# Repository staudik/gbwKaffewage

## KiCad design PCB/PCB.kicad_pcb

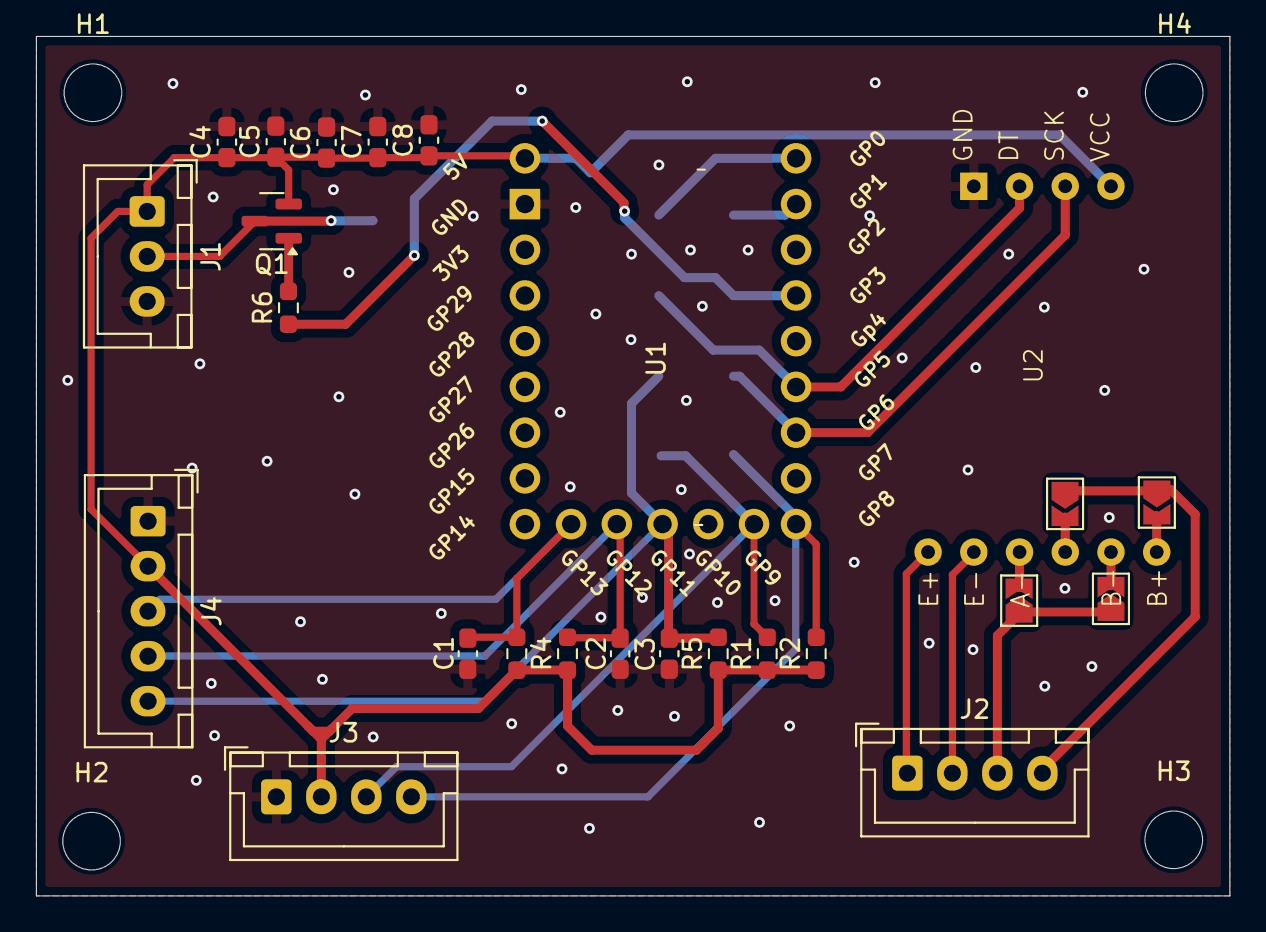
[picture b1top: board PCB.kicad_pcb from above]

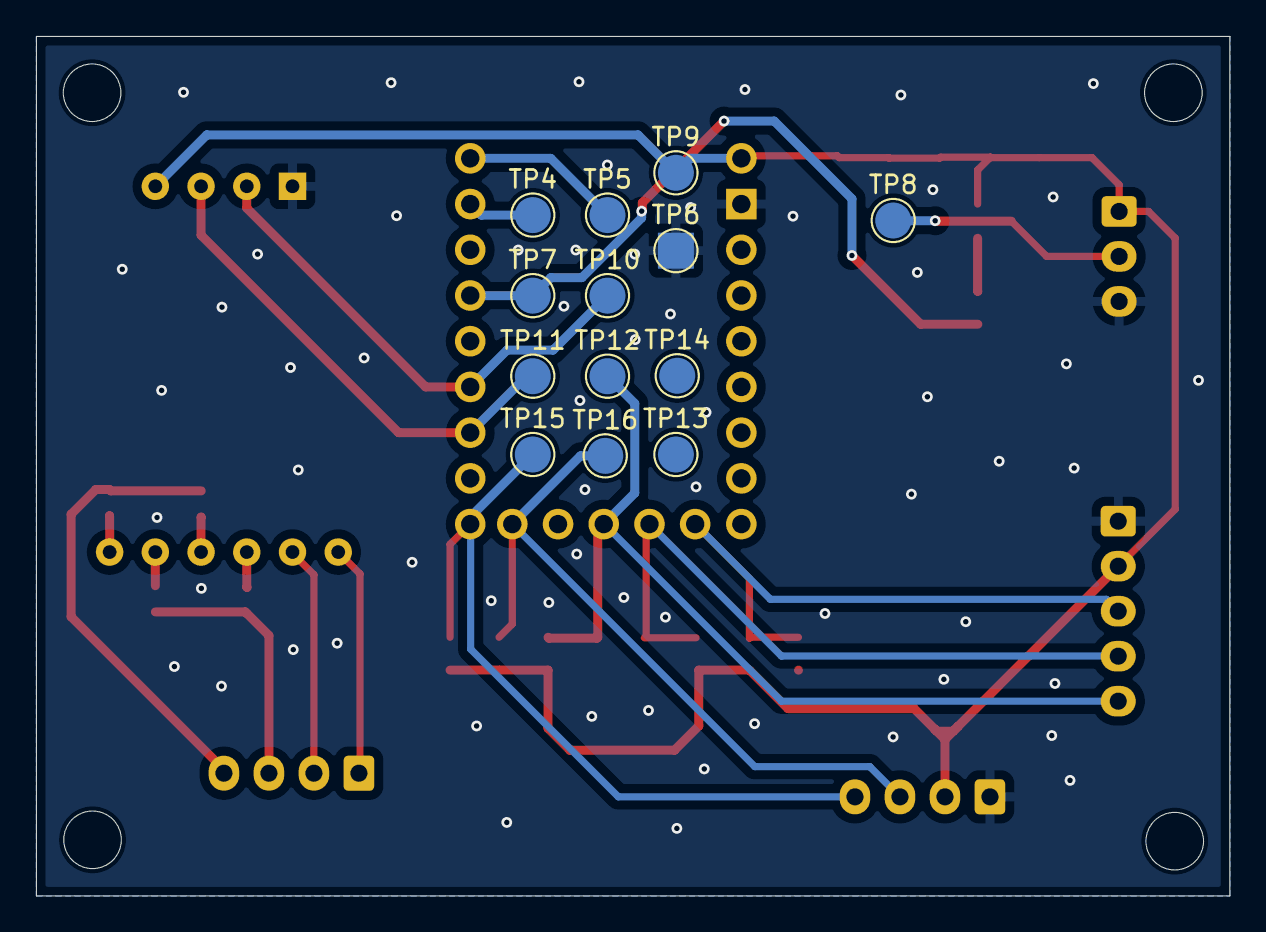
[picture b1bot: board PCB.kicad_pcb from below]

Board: 2 copper layers, 66.3 x 47.8 mm, 42 parts (13 on the bottom side), 22 nets.

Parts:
C1, C2, C3: 100n; C_0603_1608Metric_Pad1.08x0.95mm_HandSolder
C4, C5, C6, C7, C8: C; C_0603_1608Metric_Pad1.08x0.95mm_HandSolder
H1, H2, H3, H4: MountingHole; MountingHole_3.2mm_M3_DIN965
J1: Conn_01x03_Pin; JST_XH_B3B-XH-A_1x03_P2.50mm_Vertical
J2: Conn_01x04_Pin; JST_XH_B4B-XH-A_1x04_P2.50mm_Vertical
J3: Conn_01x04_Socket; JST_XH_B4B-XH-A_1x04_P2.50mm_Vertical
J4: Conn_01x05_Socket; JST_XH_B5B-XH-A_1x05_P2.50mm_Vertical
JP1, JP2, JP3, JP4: SolderJumper_2_Open; SolderJumper-2_P1.3mm_Open_TrianglePad1.0x1.5mm
Q1: BC807; SOT-23
R1, R2, R3, R4, R5, R6: 3.3k; R_0603_1608Metric_Pad0.98x0.95mm_HandSolder
TP4, TP5, TP6, TP7, TP8, TP9, TP10, TP11, TP12, TP13, TP14, TP15, TP16: TestPoint; TestPoint_Pad_D2.0mm
U1: Pico; RPi_Pico_SMD_micro_version
U2: HX711; hx711_module

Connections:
+5V: C4.1, C5.1, C6.1, C7.1, C8.1, J1.1, J3.2, J4.2, Q1.2 (E), R1.1, R2.1, R3.1, R4.1, R5.1, TP9.1, U1.40 (VBUS), U2.VCC
/HX711_SCK: TP11.1, U1.9 (GPIO6), U2.SCK
/HX/11_DT: TP10.1, U1.7 (GPIO5), U2.DT
/LCD_SCL: J3.3, R1.2, TP16.1, U1.12 (GPIO9)
/LCD_SDA: J3.4, R2.2, TP15.1, U1.11 (GPIO8)
/Relay: J1.2, Q1.3 (C), TP8.1
/Relay_3.3: R6.1, TP7.1, U1.5 (GPIO3)
/encoder_a: C1.1, J4.3, R3.2, U1.17 (GPIO13)
/encoder_b: C2.1, J4.4, R4.2, U1.16 (GPIO12)
/encoder_button: C3.1, J4.5, R5.2, TP12.1, U1.15 (GPIO11)
GND: C1.2, C2.2, C3.2, C4.2, C5.2, C6.2, C7.2, C8.2, J1.3, J3.1, J4.1, TP6.1, U1.3 (GND), U2.GND_D
unnamed: J2.1, U2.E+
unnamed: J2.2, U2.E-_GND_A
unnamed: J2.3, JP3.1 (A), JP4.1 (A)
unnamed: J2.4, JP1.1 (A), JP2.1 (A)
unnamed: JP1.2 (B), U2.B+
unnamed: JP2.2 (B), U2.A+
unnamed: JP3.2 (B), U2.A-
unnamed: JP4.2 (B), U2.B-
unnamed: Q1.1 (B), R6.2
unnamed: TP5.1, U1.1 (GPIO0)
unnamed: TP4.1, U1.2 (GPIO1)

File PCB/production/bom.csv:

Designator,Footprint,Quantity,Value,LCSC Part #
"C1, C2, C3",0603,3,100n,
"C4, C5, C6, C7, C8",0603,5,C,
J1,JST_XH_B3B-XH-A_1x03_P2.50mm_Vertical,1,Conn_01x03_Pin,
J2,JST_XH_B4B-XH-A_1x04_P2.50mm_Vertical,1,Conn_01x04_Pin,
J3,JST_XH_B4B-XH-A_1x04_P2.50mm_Vertical,1,Conn_01x04_Socket,
J4,JST_XH_B5B-XH-A_1x05_P2.50mm_Vertical,1,Conn_01x05_Socket,
Q1,SOT-23,1,BC807,
"R1, R2, R3, R4, R5, R6",0603,6,3.3k,
"TP10, TP11, TP12, TP13, TP14, TP15, TP16, TP4, TP5, TP6, TP7, TP8, TP9",TestPoint_Pad_D2.0mm,13,TestPoint,
U1,RPi_Pico_SMD_micro_version,1,Pico,
U2,hx711_module,1,HX711,

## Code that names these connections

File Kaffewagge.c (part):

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#define HX711_DOUT 5
#define HX711_PD_SCK 6

#define Encoder_A 11
#define Encoder_B 12
#define Encoder_Button 13

#define GPIO_BUTTON 7
#define GPIO_RELAY 3

#define I2C_PORT i2c0
#define I2C_SDA 8
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    tarra = (float)sum / sizeTarra;
}

// interupt handler for gpio irq encoder_button
void gpio_irq_handler(uint gpio, uint32_t event_mask)
{
    if (gpio == Encoder_Button)
    {
        if (event_mask & GPIO_IRQ_EDGE_FALL)
        {
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        gpio_pull_up(I2C_SCL);

        // gpio init
        gpio_init(GPIO_RELAY);
        gpio_init(Encoder_Button);

        gpio_set_dir(GPIO_RELAY, GPIO_OUT);
        gpio_set_dir(Encoder_Button, GPIO_IN);
        gpio_disable_pulls(Encoder_Button);
        gpio_set_input_hysteresis_enabled(Encoder_Button, true);
        gpio_set_irq_enabled_with_callback(Encoder_Button, GPIO_IRQ_EDGE_FALL, true, &gpio_irq_handler);

        // sets up the pio sm for hx711
        //******************************************************
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        {
            dispState = grinding;
            taraf();
            gpio_put(GPIO_RELAY, true);
            startgrind = false;
        }

        updateWight();

        if ((whight > stopWhight + offset) && gpio_get_out_level(GPIO_RELAY))
        {
            gpio_put(GPIO_RELAY, false);
            // withing vor Wight to satel to read last whight
            for (int i = 0; i < SizeMean * 3; i++)
            {
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
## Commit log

2025-09-16 pcb added pipico and hx711; startet with layout
2025-09-16 schaltplan fertig
2026-02-14 PCB fertig
2026-03-13 PCB V1.0 orderd
2026-03-27 Disply now working
2026-03-28 display working and showing kurrent wight
2026-03-28 selection working on main Menu
2026-03-28 selection working on settings
2026-04-04 V0.9 test phase hat begonnen
2026-04-05 fehler behoben
2026-06-06 fixed problem with last whight being false, updatet to 80hz sampling
